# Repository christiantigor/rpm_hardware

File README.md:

rpm_hardware
============

Hardware of RPM

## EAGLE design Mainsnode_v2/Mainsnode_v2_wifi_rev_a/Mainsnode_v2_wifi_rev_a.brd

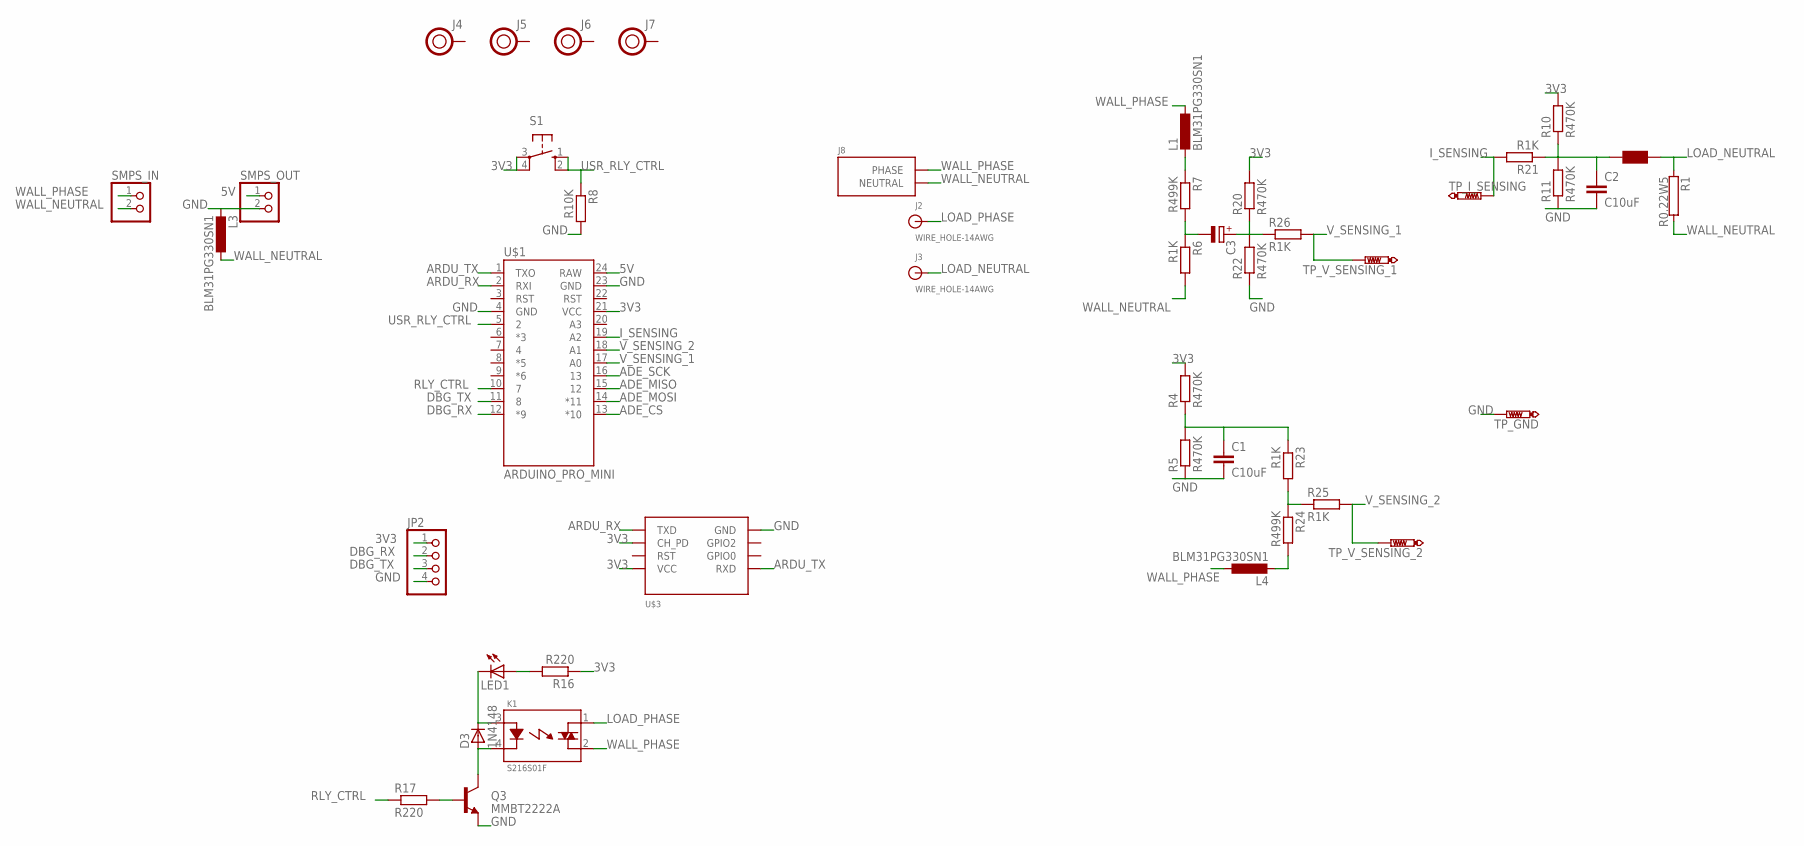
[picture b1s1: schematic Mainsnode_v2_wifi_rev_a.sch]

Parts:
C1, C2: C10uF; C0805
C3: CPOL-EU140CLH-0810; 140CLH-0810
D3: 1N4148; SOD80
J2, J3: WIRE_HOLE-14AWG
J4, J5, J6, J7: HOLE; HOLE-0.125
J8: AC-PLUG-2; AC_MALE_PINS_2
JP2: PINHD-1X4; 1X04
K1: S216S01F; RELAY_SX16S0X
L1, L3, L4: BLM31PG330SN1; L3216C
LED1: LED3MM
Q3: MMBT2222A; SOT23-3
R1: R0.22W5; KH206-8
R4, R5, R10, R11, R20, R22: R470K; R0805
R6, R21, R23, R25, R26: R1K; R0805
R7, R24: R499K; R0805
R8: R10K; R0805
R16, R17: R220; R0805
S1: 10-XX; B3F-10XX
SMPS_IN: PINHD-1X2; 1X02
SMPS_OUT: PINHD-1X2; 1X02
TP_GND: PTR1PAD1-13; P1-13
TP_I_SENSING: PTR1PAD1-13; P1-13
TP_V_SENSING_1, TP_V_SENSING_2: PTR1PAD1-13; P1-13
U$1: ARDUINO_PRO_MINI
U$2: BLM18BB151SN1; L0603
U$3: ESP8266

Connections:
3V3: JP2.1, R4.2, R10.2, R16.1, R20.2, S1.3, S1.4 (P1), U$1.21 (VCC), U$3.CH_PD, U$3.VCC
5V: SMPS_OUT.1, U$1.24 (RAW)
ADE_CS: U$1.13 (*10)
ADE_MISO: U$1.15 (12)
ADE_MOSI: U$1.14 (*11)
ADE_SCK: U$1.16 (13)
ARDU_RX: U$1.2 (RXI), U$3.TXD
ARDU_TX: U$1.1 (TXO), U$3.RXD
DBG_RX: JP2.2, U$1.12 (*9)
DBG_TX: JP2.3, U$1.11 (8)
GND: C1.2, C2.2, JP2.4, L3.2, Q3.2 (E), R5.1, R8.2, R11.1, R22.1, SMPS_OUT.2, TP_GND.TP, U$1.4 (GND), U$1.23 (GND), U$3.GND
I_SENSING: R21.2, TP_I_SENSING.TP, U$1.19 (A2)
LOAD_NEUTRAL: J3.P$1, R1.1, U$2.2
LOAD_PHASE: J2.P$1, K1.1
unnamed: C3.-, R6.1, R7.2
unnamed: C3.+, R20.1, R22.2, R26.1
unnamed: C2.1, R10.1, R11.2, R21.1, U$2.1
unnamed: C1.1, R4.1, R5.2, R23.1
unnamed: L1.2, R7.1
unnamed: R23.2, R24.1, R25.1
unnamed: LED1.A, R16.2
unnamed: L4.2, R24.2
unnamed: D3.1 (C), K1.3, LED1.K (C)
unnamed: D3.2 (A), K1.4, Q3.3 (C)
unnamed: Q3.1 (B), R17.2
RLY_CTRL: R17.1, U$1.10 (7)
USR_RLY_CTRL: R8.1, S1.1 (S), S1.2 (S1), U$1.5 (2)
V_SENSING_1: R26.2, TP_V_SENSING_1.TP, U$1.17 (A0)
V_SENSING_2: R25.2, TP_V_SENSING_2.TP, U$1.18 (A1)
WALL_NEUTRAL: J8.WALL_NEUTRAL (NEUTRAL), L3.1, R1.2, R6.2, SMPS_IN.2
WALL_PHASE: J8.WALL_PHASE (PHASE), K1.2, L1.1, L4.1, SMPS_IN.1

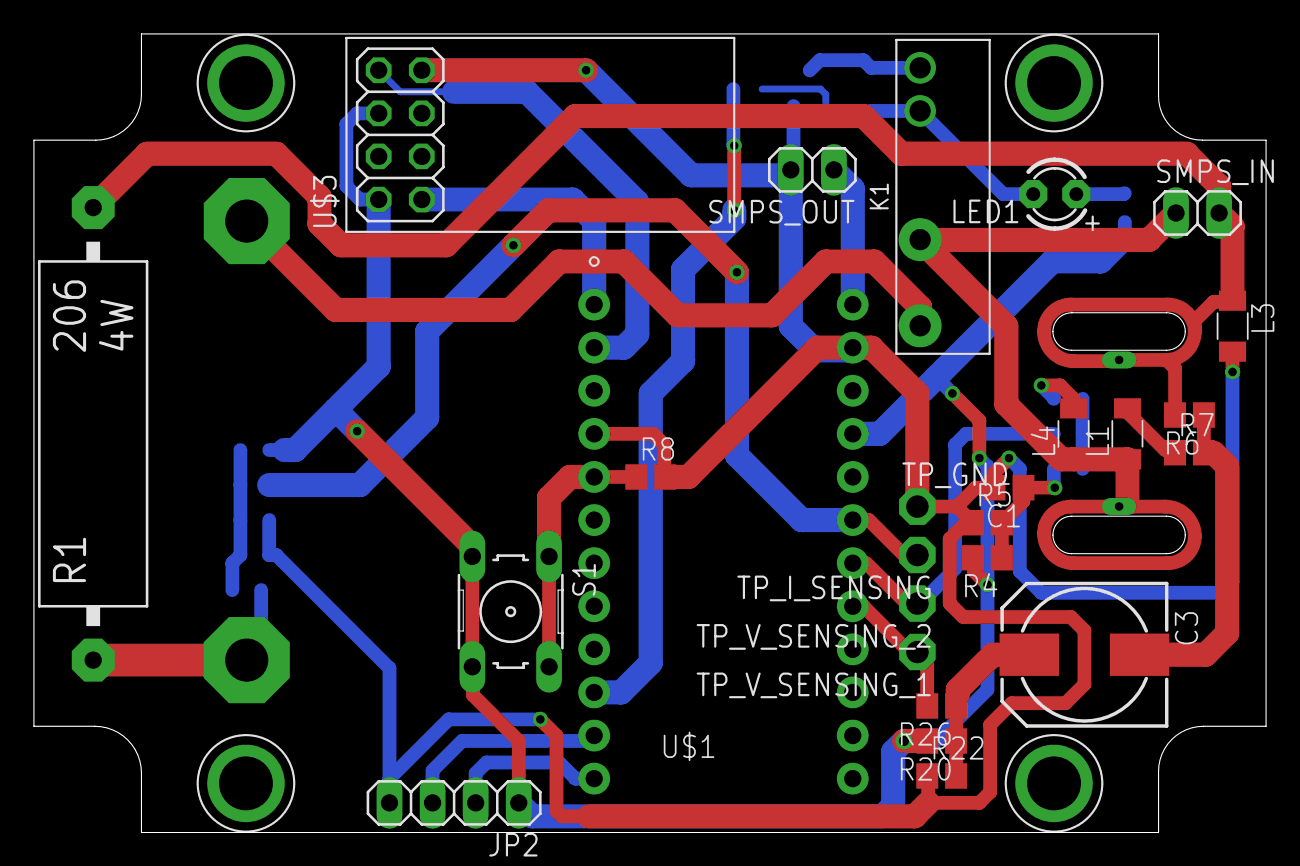
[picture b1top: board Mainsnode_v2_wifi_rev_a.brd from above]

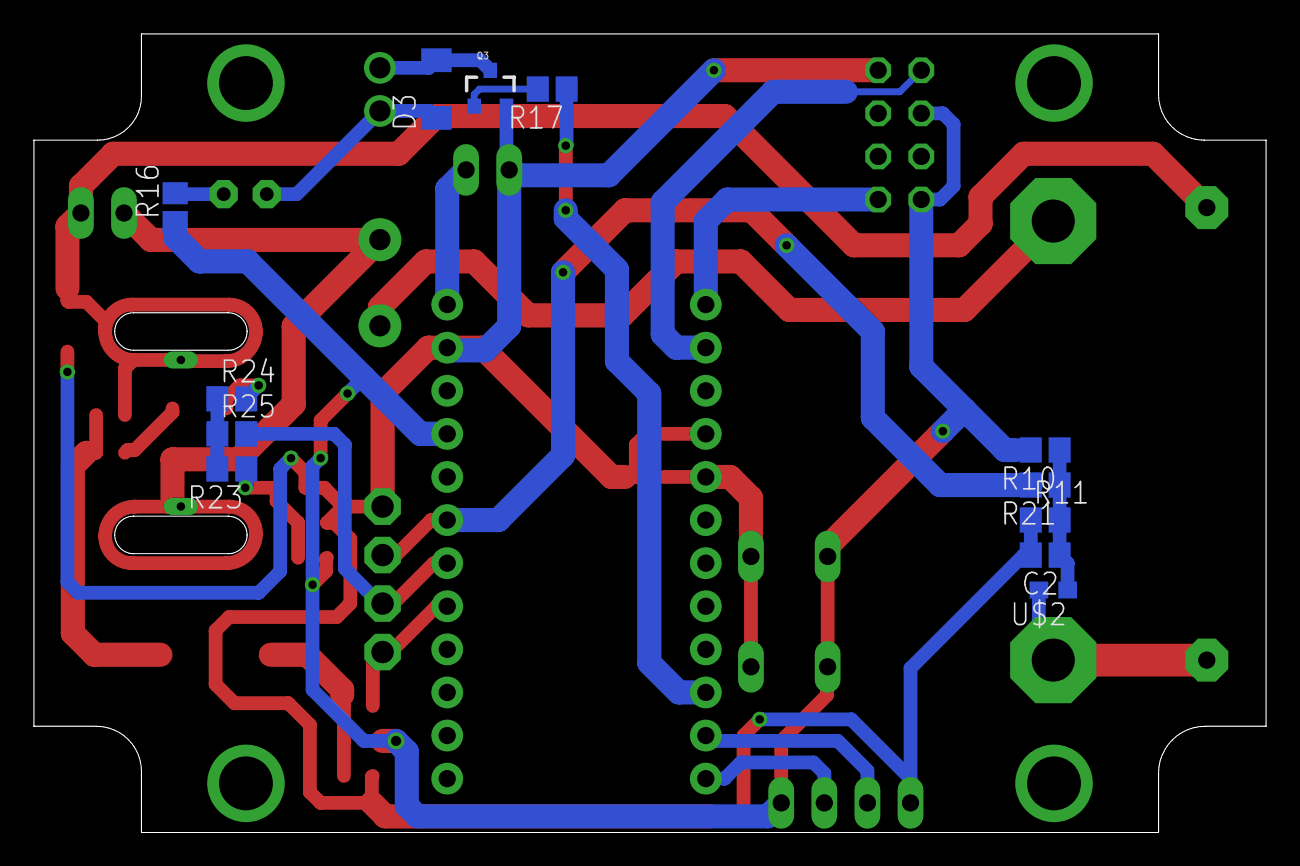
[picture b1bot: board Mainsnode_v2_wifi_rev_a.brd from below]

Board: 2 copper layers, 72.6 x 47.1 mm, 45 parts (12 on the bottom side), 27 nets.

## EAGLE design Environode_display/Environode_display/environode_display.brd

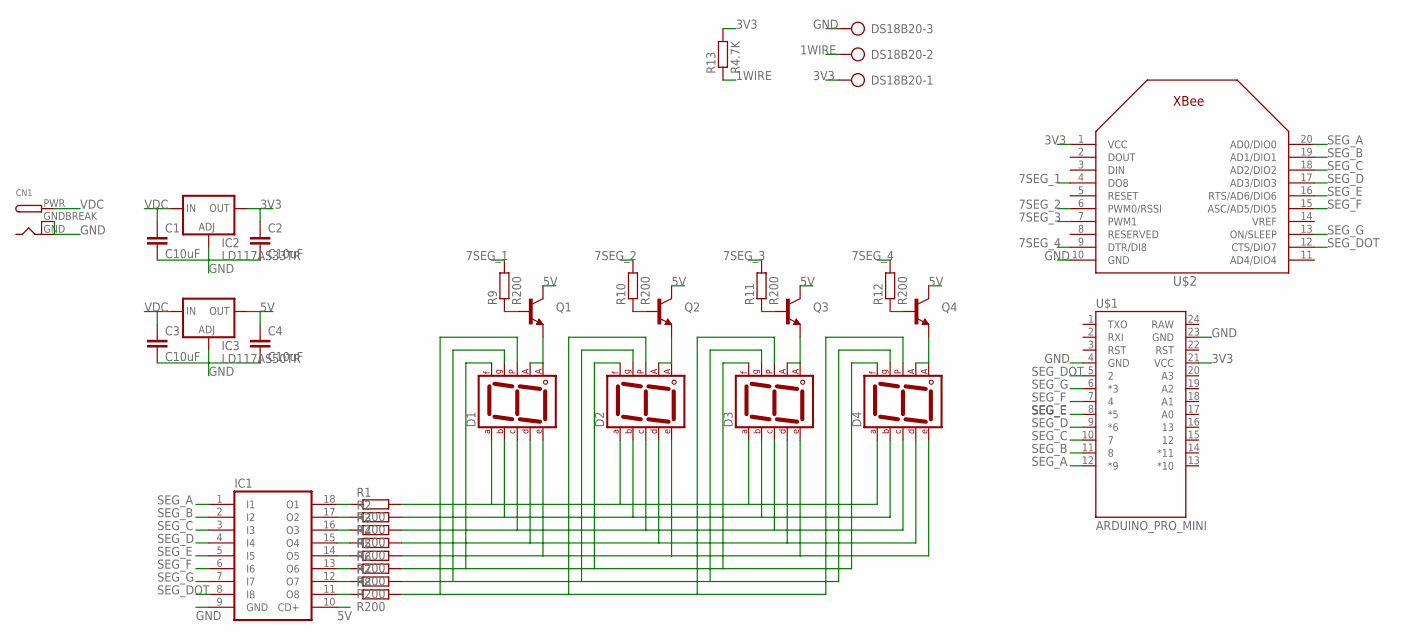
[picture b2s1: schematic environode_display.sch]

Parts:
C1, C2, C3, C4: C10uF; C0805
CN1: DCBARRELPTH; DCJACK_2MM_PTH
D1, D2, D3, D4: 7SEG-CA; 7SEG-13
DS18B20: AK300/3
IC1: ULN2803A; DIL18
IC2: LD117AS33TR; SOT223
IC3: LD117AS50TR; SOT223
Q1, Q2, Q3, Q4: TRANSISTOR_NPNP2N2222A; TO-92
R1, R2, R3, R4, R5, R6, R7, R8, R9, R10, R11, R12: R200; 0309V
R13: R4.7K; 0309V
U$1: ARDUINO_PRO_MINI
U$2: XBEE

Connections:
1WIRE: DS18B20.2, R13.1
3V3: C2.1, DS18B20.1, IC2.4 (OUT), R13.2, U$1.21 (VCC), U$2.1 (VCC)
5V: C4.1, IC1.10 (CD+), IC3.4 (OUT), Q1.1 (C), Q2.1 (C), Q3.1 (C), Q4.1 (C)
7SEG_1: R9.2, U$2.4 (DO8)
7SEG_2: R10.2, U$2.6 (PWM0/RSSI)
7SEG_3: R11.2, U$2.7 (PWM1)
7SEG_4: R12.2, U$2.9 (DTR/DI8)
GND: C1.2, C2.2, C3.2, C4.2, CN1.GND, CN1.GNDBREAK, DS18B20.3, IC1.9 (GND), IC2.1 (ADJ), IC3.1 (ADJ), U$1.4 (GND), U$1.23 (GND), U$2.10 (GND)
unnamed: IC1.18 (O1), R1.1
unnamed: IC1.17 (O2), R2.1
unnamed: IC1.16 (O3), R3.1
unnamed: IC1.15 (O4), R4.1
unnamed: IC1.14 (O5), R5.1
unnamed: IC1.13 (O6), R6.1
unnamed: IC1.12 (O7), R7.1
unnamed: IC1.11 (O8), R8.1
unnamed: D1.7 (A), D2.7 (A), D3.7 (A), D4.7 (A), R1.2
unnamed: D1.6 (B), D2.6 (B), D3.6 (B), D4.6 (B), R2.2
unnamed: D1.4 (C), D2.4 (C), D3.4 (C), D4.4 (C), R3.2
unnamed: D1.2 (D), D2.2 (D), D3.2 (D), D4.2 (D), R4.2
unnamed: D1.1 (E), D2.1 (E), D3.1 (E), D4.1 (E), R5.2
unnamed: D1.9 (F), D2.9 (F), D3.9 (F), D4.9 (F), R6.2
unnamed: D1.10 (G), D2.10 (G), D3.10 (G), D4.10 (G), R7.2
unnamed: D1.3 (CA1), D1.8 (CA2), Q1.3 (E)
unnamed: D2.3 (CA1), D2.8 (CA2), Q2.3 (E)
unnamed: Q1.2 (B), R9.1
unnamed: D1.5 (DP), D2.5 (DP), D3.5 (DP), D4.5 (DP), R8.2
unnamed: D3.3 (CA1), D3.8 (CA2), Q3.3 (E)
unnamed: Q2.2 (B), R10.1
unnamed: D4.3 (CA1), D4.8 (CA2), Q4.3 (E)
unnamed: Q3.2 (B), R11.1
unnamed: Q4.2 (B), R12.1
SEG_A: IC1.1 (I1), U$1.12 (*9), U$2.20 (AD0/DIO0)
SEG_B: IC1.2 (I2), U$1.11 (8), U$2.19 (AD1/DIO1)
SEG_C: IC1.3 (I3), U$1.10 (7), U$2.18 (AD2/DIO2)
SEG_D: IC1.4 (I4), U$1.9 (*6), U$2.17 (AD3/DIO3)
SEG_DOT: IC1.8 (I8), U$1.5 (2), U$2.12 (CTS/DIO7)
SEG_E: IC1.5 (I5), U$1.8 (*5), U$2.16 (RTS/AD6/DIO6)
SEG_F: IC1.6 (I6), U$1.7 (4), U$2.15 (ASC/AD5/DIO5)
SEG_G: IC1.7 (I7), U$1.6 (*3), U$2.13 (ON/SLEEP)
VDC: C1.1, C3.1, CN1.PWR, IC2.3 (IN), IC3.3 (IN)

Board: 2 copper layers, 32 parts (0 on the bottom side), 41 nets, no tracks yet.

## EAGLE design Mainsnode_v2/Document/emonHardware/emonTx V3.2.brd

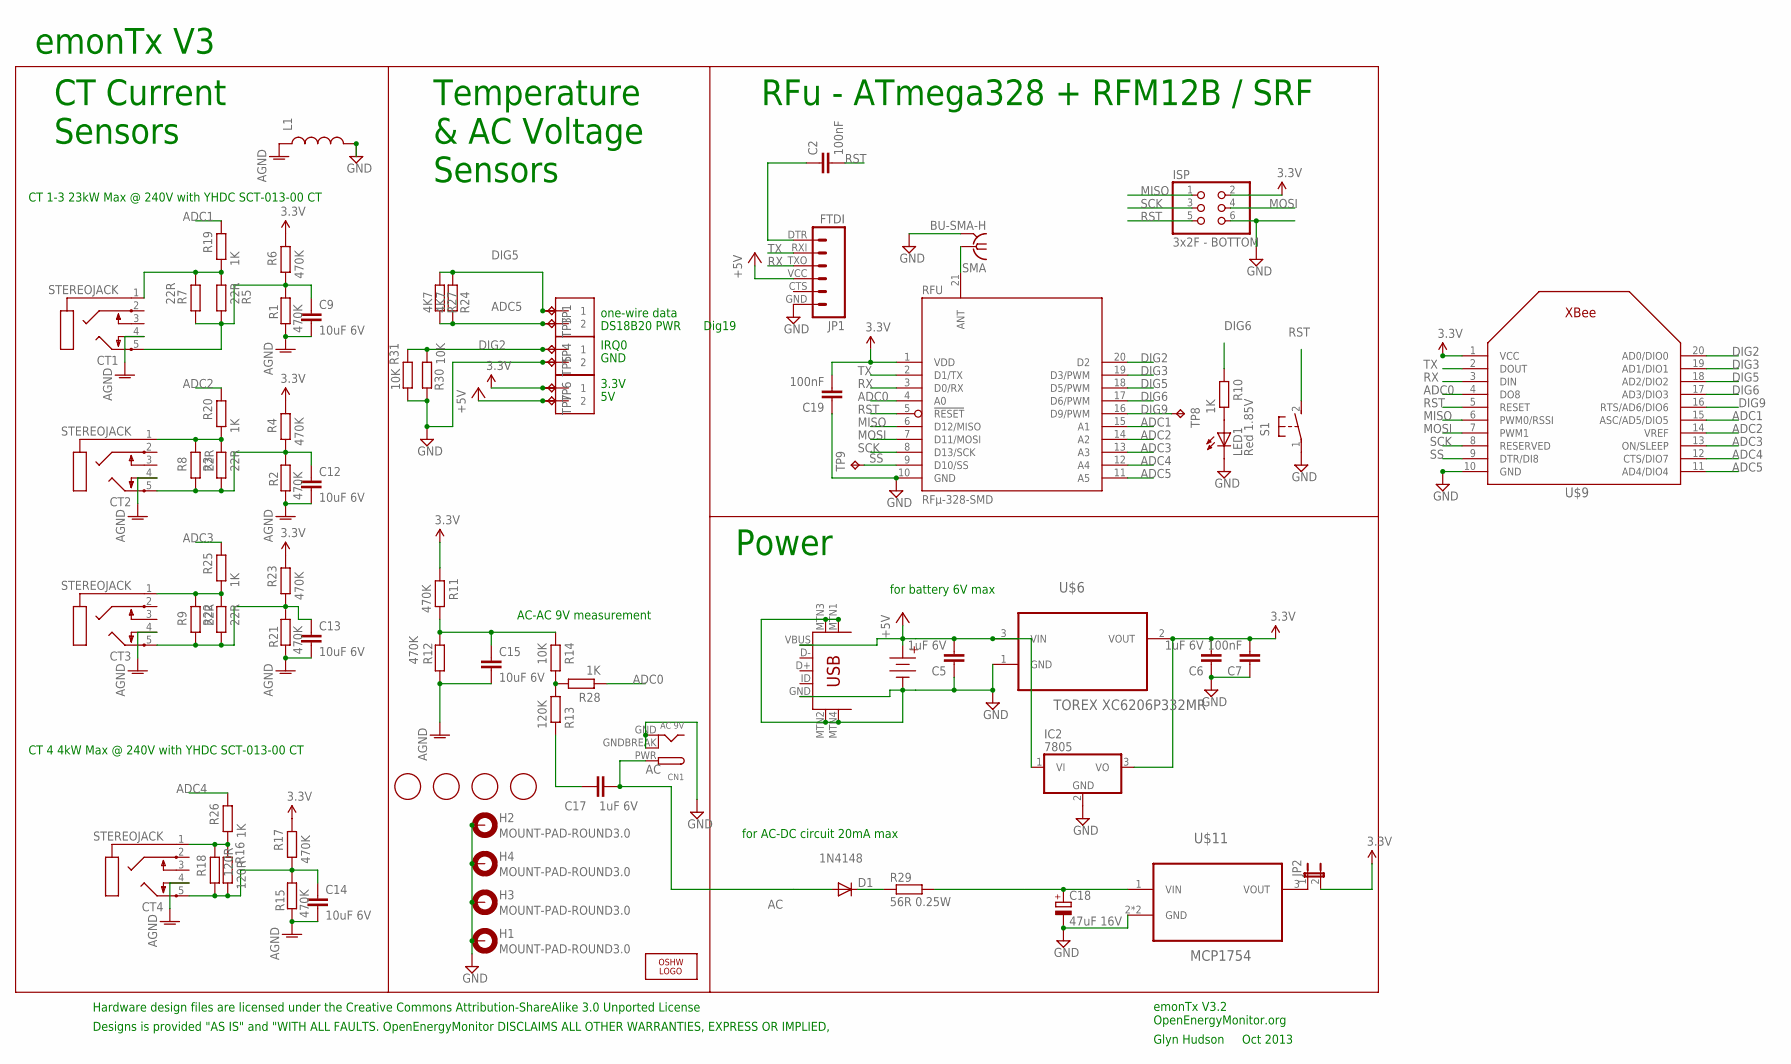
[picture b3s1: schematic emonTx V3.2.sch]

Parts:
C2, C7, C19: 100nF; C0603
C5, C6, C17: 1uF 6V; C0603
C9, C12, C13, C14, C15: 10uF 6V; C0603
C18: 47uF 16V; PANASONIC_D
CN1: AC 9V; DCJACK_2MM_PTH
CT1, CT2, CT3, CT4: STEREOJACK; STX3100
D1: 1N4148; SOD-323
H1, H2, H3, H4: MOUNT-PAD-ROUND3.0; 3,0-PAD
IC2: 7805; TO220V
ISP: 3x2F - BOTTOM; 2X03
J1, J2, J4: 1X2-3.5MM
JP1: FTDI; FTDI_BASIC
JP2: JUMPER-2PTH_LOCK; 1X02_LOCK
L1: INDUCTOR0603; 0603
LED1: Red 1.85V; CHIP-LED0805
LOGO1: OSHW_LOGO_6MILX0200-NT; OSHW_6X200_NOTEXT
R1, R2, R4, R6, R11, R12, R15, R17, R21, R23: 470K; R0603
R3, R5, R22: 22R; 0204/7
R7, R8, R9: 22R; R1206
R10, R19, R20, R25, R26, R28: 1K; R0603
R13: 120K; R0603
R14, R31: 10K; R0603
R16: 120R; 0204/7
R18: 120R; R1206
R24: 4K7; 0204/7
R27: 4K7; R0603
R29: 56R 0.25W; R1206
R30: 10K; 0204/7
RFU: RFµ-328-SMD; RFµ-328-LANDING
S1: 31-XX; B3F-31XX
SMA: BU-SMA-H
TP1, TP3, TP4, TP5, TP6, TP7, TP8, TP9: TPPAD1-13; P1-13
U$1, U$4, U$5, U$7: FIDUCIAL; FIDUCIAL_1MM
U$3: 4.5V; AAA_PCB_HOLDER
U$6: TOREX XC6206P332MR; SOT95P237X112-3N
U$9: XBEE
U$10: USB-MINIB-5PIN; USB-MINIB-CISECO
U$11: MCP1754; SOT89

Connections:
3.3V: C6.2, C7.2, C19.2, IC2.3 (VO), ISP.2, J4.1, JP2.2, R4.2, R6.2, R11.2, R17.2, R23.2, RFU.1 (VDD), TP6.TP, U$6.2 (VOUT), U$9.1 (VCC)
+5V: C5.2, IC2.1 (VI), J4.2, JP1.VCC (4), TP7.TP, U$3.+, U$6.3 (VIN), U$10.VBUS
AC: C17.2, CN1.PWR, D1.2 (A)
ADC0: R28.1, RFU.4 (A0), U$9.4 (DO8)
ADC1: R19.2, RFU.15 (A1), U$9.15 (ASC/AD5/DIO5)
ADC2: R20.2, RFU.14 (A2), U$9.14 (VREF)
ADC3: R25.2, RFU.13 (A3), U$9.13 (ON/SLEEP)
ADC4: R26.2, RFU.12 (A4), U$9.12 (CTS/DIO7)
ADC5: J2.2, R24.2, R27.2, RFU.11 (A5), TP3.TP, U$9.11 (AD4/DIO4)
AGND: C9.2, C12.2, C13.2, C14.2, C15.2, CT1.4, CT2.4, CT3.4, CT4.4, L1.1, R1.2, R2.2, R12.1, R15.2, R21.2
DIG2: J1.1, R30.1, R31.1, RFU.20 (D2), TP4.TP, U$9.20 (AD0/DIO0)
DIG3: RFU.19 (D3/PWM), U$9.19 (AD1/DIO1)
DIG5: J2.1, R24.1, R27.1, RFU.18 (D5/PWM), TP1.TP, U$9.18 (AD2/DIO2)
DIG6: R10.2, RFU.17 (D6/PWM), U$9.17 (AD3/DIO3)
DIG9: RFU.16 (D9/PWM), TP8.TP, U$9.16 (RTS/AD6/DIO6)
GND: C5.1, C6.1, C7.1, C18.-, C19.1, CN1.GND, CN1.GNDBREAK, H1.B3,0, H2.B3,0, H3.B3,0, H4.B3,0, IC2.2 (GND), ISP.6, J1.2, JP1.GND (6), L1.2, LED1.C, R30.2, R31.2, RFU.10 (GND), S1.1, SMA.2, SMA.3 (2), SMA.4 (2), SMA.5 (2), TP5.TP, U$3.-, U$6.1 (GND), U$9.10 (GND), U$10.GND, U$10.MTN1 (MTN2), U$10.MTN2 (MTN3), U$10.MTN3 (MTN1), U$10.MTN4, U$11.2 (GND), U$11.2.1 (GND)
MISO: ISP.1, RFU.6 (D12/MISO), U$9.6 (PWM0/RSSI)
MOSI: ISP.4, RFU.7 (D11/MOSI), U$9.7 (PWM1)
unnamed: CT1.1, R5.2, R7.2, R19.1
unnamed: C13.1, CT3.5, R9.1, R21.1, R22.1, R23.1
unnamed: R13.2, R14.1, R28.2
unnamed: JP2.1, U$11.3 (VOUT)
unnamed: C18.+, R29.2, U$11.1 (VIN)
unnamed: C17.1, R13.1
unnamed: CT4.1, R16.2, R18.2, R26.1
unnamed: C2.1, JP1.DTR (1)
unnamed: CT2.1, R3.2, R8.2, R20.1
unnamed: RFU.21 (ANT), SMA.1
unnamed: D1.1 (C), R29.1
unnamed: CT3.1, R9.2, R22.2, R25.1
unnamed: C12.1, CT2.5, R2.1, R3.1, R4.1, R8.1
unnamed: C15.1, R11.1, R12.2, R14.2
unnamed: C14.1, CT4.5, R15.1, R16.1, R17.1, R18.1
unnamed: C9.1, CT1.5, R1.1, R5.1, R6.1, R7.1
unnamed: LED1.A, R10.1
RST: C2.2, ISP.5, RFU.5 (!RESET), S1.2 (S), U$9.5 (RESET)
RX: JP1.TXO (3), RFU.3 (D0/RX), U$9.3 (DIN)
SCK: ISP.3, RFU.8 (D13/SCK), U$9.8 (RESERVED)
SS: RFU.9 (D10/SS), TP9.TP, U$9.9 (DTR/DI8)
TX: JP1.RXI (2), RFU.2 (D1/TX), U$9.2 (DOUT)

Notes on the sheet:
AC-AC 9V measurement
emonTx V3.2 OpenEnergyMonitor.org
Glyn Hudson Oct 2013
CT 4 4kW Max @ 240V with YHDC SCT-013-00 CT
CT 1-3 23kW Max @ 240V with YHDC SCT-013-00 CT
for battery 6V max
for AC-DC circuit 20mA max
Dig19
Power
RFu - ATmega328 + RFM12B / SRF
CT Current Sensors
Temperature & AC Voltage Sensors
Designs is provided "AS IS" and "WITH ALL FAULTS. OpenEnergyMonitor DISCLAIMS ALL OTHER WARRANTIES, EXPRESS OR IMPLIED,
Hardware design files are licensed under the Creative Commons Attribution-ShareAlike 3.0 Unported License
emonTx V3
DS18B20 PWR
one-wire data
IRQ0
GND
3.3V

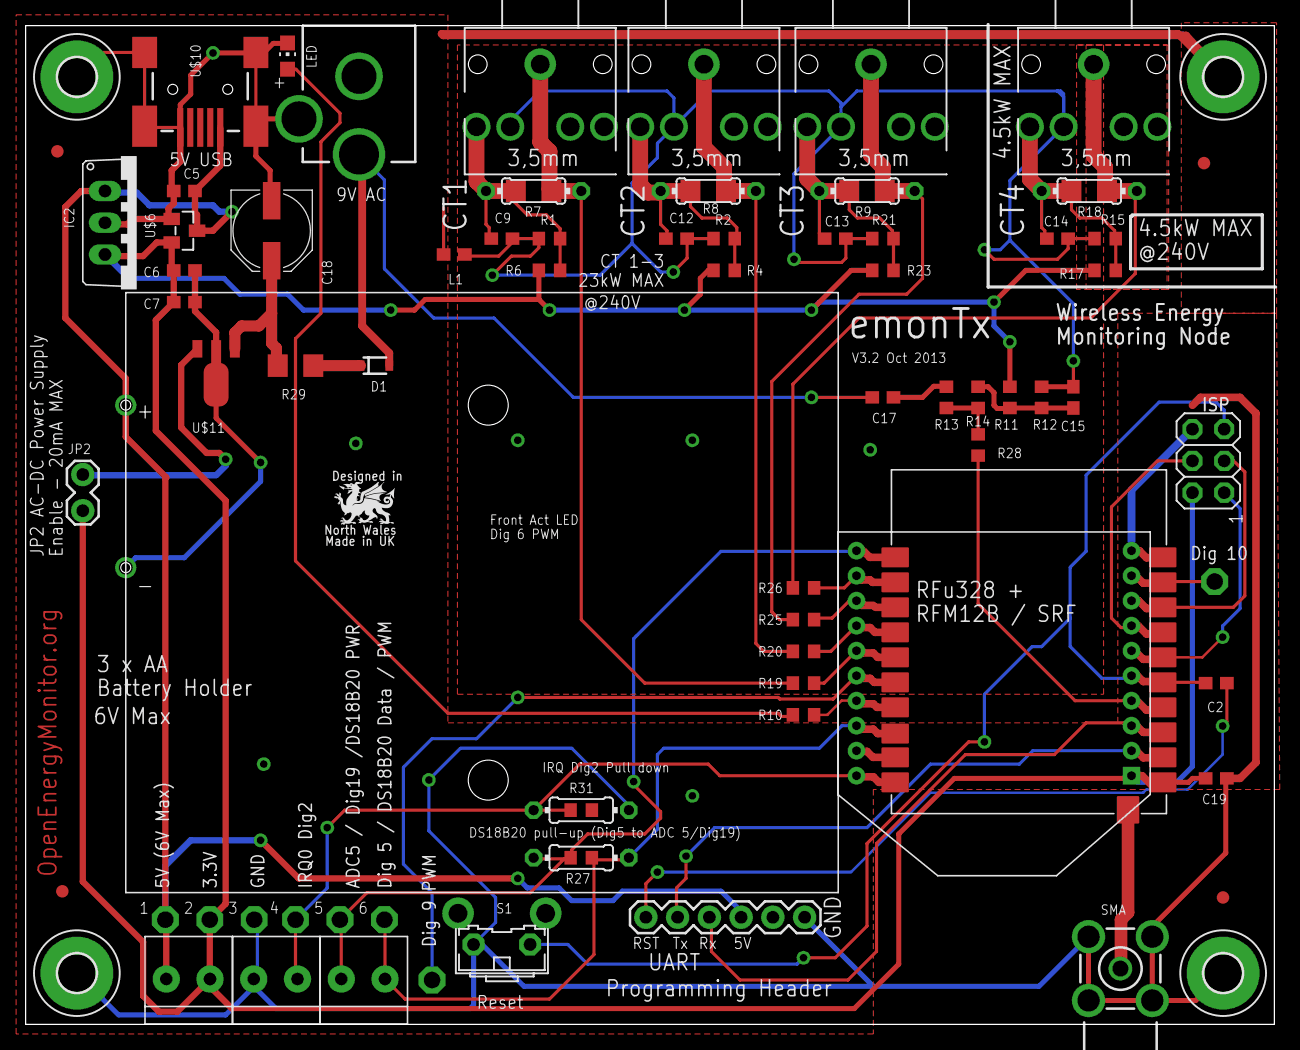
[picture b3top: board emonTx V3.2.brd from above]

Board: 2 copper layers, 99.9 x 79.9 mm, 83 parts (1 on the bottom side), 40 nets.

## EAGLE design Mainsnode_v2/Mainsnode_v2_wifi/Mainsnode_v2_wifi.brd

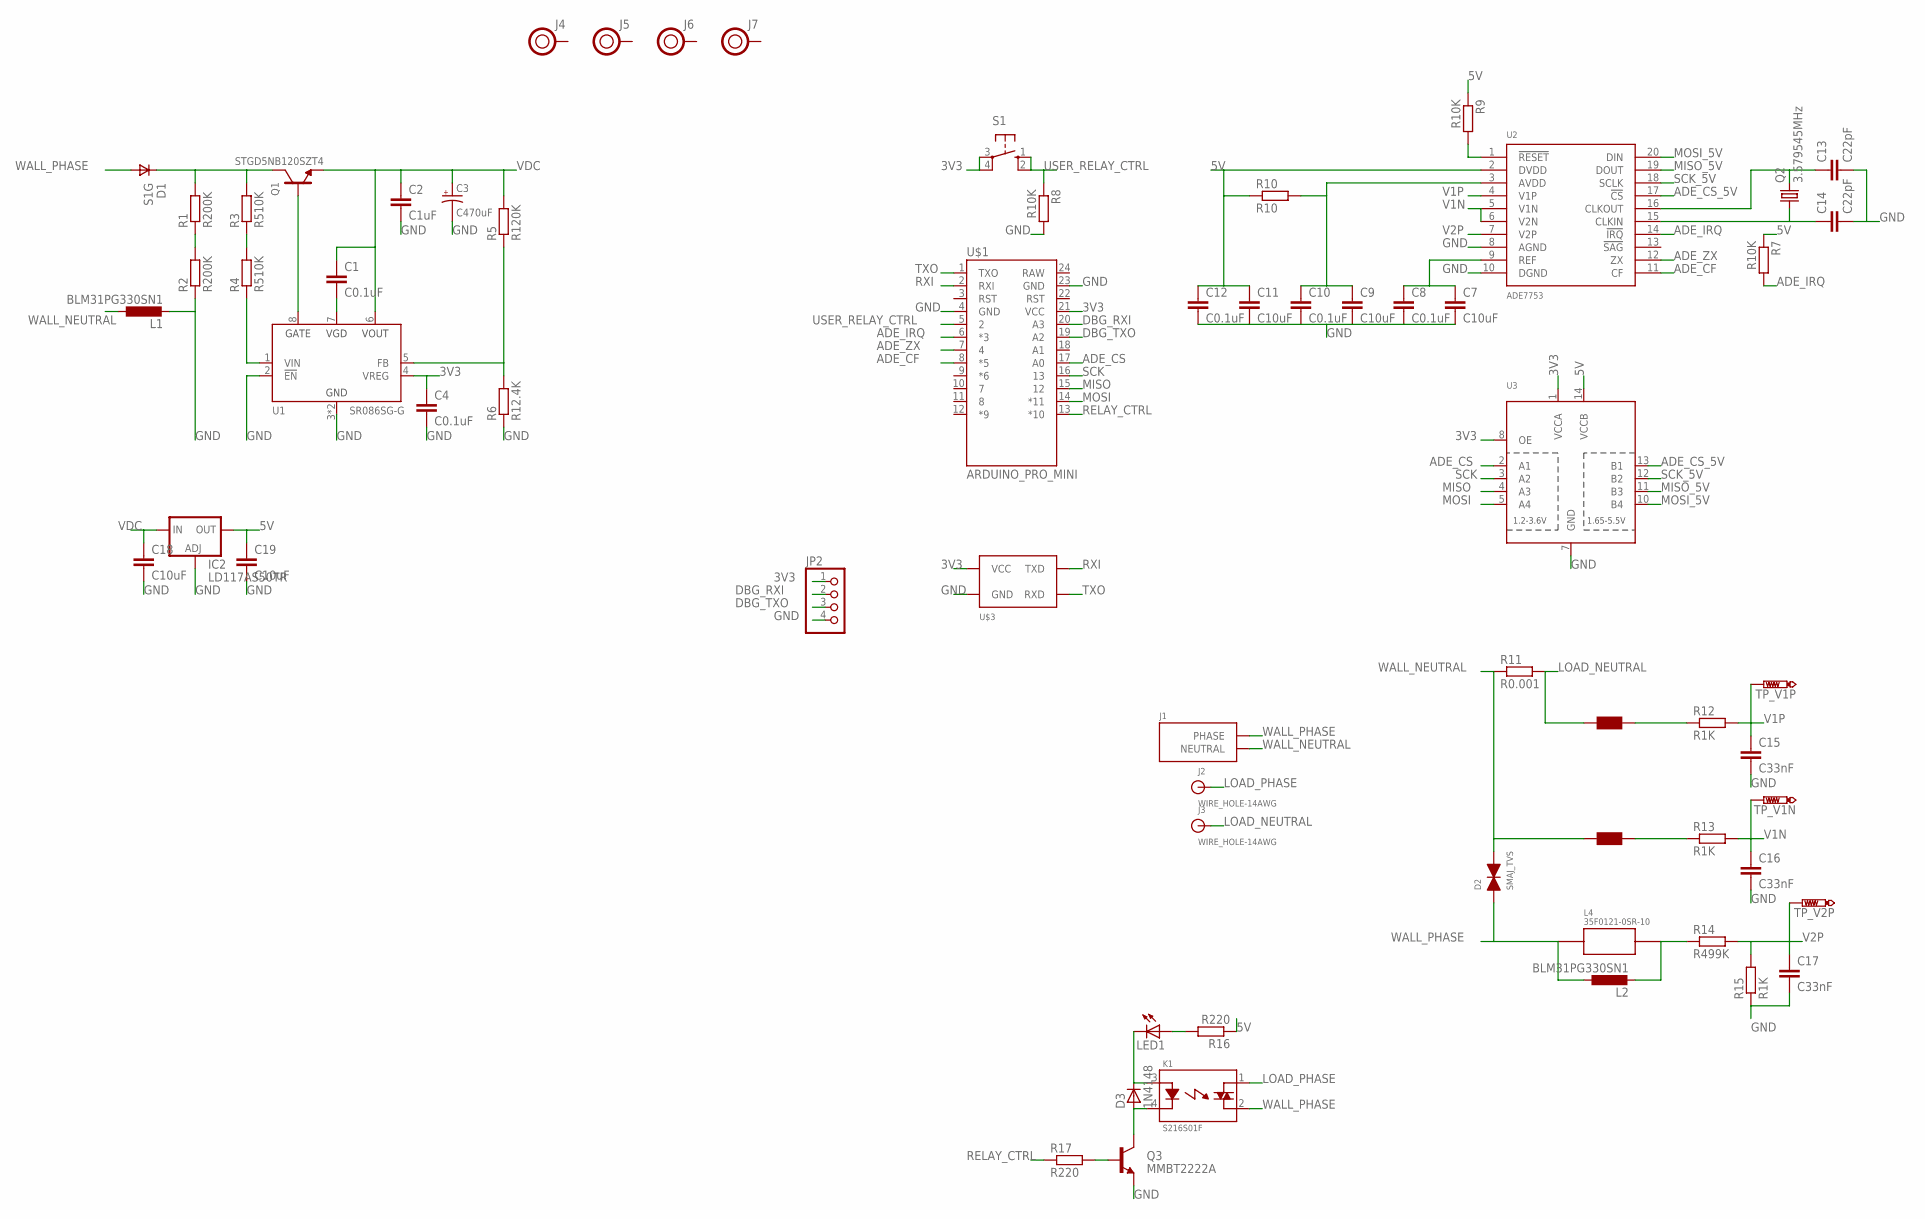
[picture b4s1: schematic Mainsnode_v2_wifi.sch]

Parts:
C1, C4, C8, C10, C12: C0.1uF; C0805
C2: C1uF; C0805
C3: C470uF; CAP_SM_10MM
C7, C9, C11, C18, C19: C10uF; C0805
C13, C14: C22pF; C0805
C15, C16, C17: C33nF; C0805
D1: S1G; DO-214AC
D2: SMAJ_TVS; DO214_TVS
D3: 1N4148; SOD80
IC2: LD117AS50TR; SOT223
J1: AC-PLUG-2; AC_MALE_PINS_2
J2, J3: WIRE_HOLE-14AWG
J4, J5, J6, J7: HOLE; HOLE-0.125
JP2: PINHD-1X4; 1X04
K1: S216S01F; RELAY_SX16S0X
L1, L2: BLM31PG330SN1; L3216C
L4: 35F0121-0SR-10; 35F0102
LED1: LED3MM
Q1: STGD5NB120SZT4; DPAK
Q2: 3.579545MHz; HC49/S
Q3: MMBT2222A; SOT23-3
R1, R2: R200K; M0805
R3, R4: R510K; M0805
R5: R120K; M0805
R6: R12.4K; M0805
R7, R8, R9: R10K; R0805
R10: R10; R0805
R11: R0.001; R2512
R12, R13, R15: R1K; R0805
R14: R499K; R0805
R16, R17: R220; R0805
S1: 10-XX; B3F-10XX
TP_V1N, TP_V1P, TP_V2P: PTR1PAD1-13; P1-13
U1: SR086SG-G; SR086
U2: ADE7753; SSOP-20
U3: TXB0104PWR; TSSOP14
U$1: ARDUINO_PRO_MINI
U$3: ESP8266
U$4, U$5: BLM18BB151SN1; L0603

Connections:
3V3: C4.1, JP2.1, S1.3, S1.4 (P1), U1.4 (VREG), U3.1 (VCCA), U3.8 (OE), U$1.21 (VCC), U$3.VCC
5V: C11.1, C12.1, C19.1, IC2.4 (OUT), R7.1, R9.1, R10.1, R16.1, U2.2 (DVDD), U3.14 (VCCB)
ADE_CF: U2.11 (CF), U$1.8 (*5)
ADE_CS: U3.2 (A1), U$1.17 (A0)
ADE_CS_5V: U2.17 (!CS), U3.13 (B1)
ADE_IRQ: R7.2, U2.14 (!IRQ), U$1.6 (*3)
ADE_ZX: U2.12 (ZX), U$1.7 (4)
DBG_RXI: JP2.2, U$1.20 (A3)
DBG_TXO: JP2.3, U$1.19 (A2)
GND: C2.2, C3.-, C4.2, C7.2, C8.2, C9.2, C10.2, C11.2, C12.2, C13.2, C14.2, C15.2, C16.2, C17.2, C18.2, C19.2, IC2.1 (ADJ), JP2.4, L1.2, Q3.2 (E), R2.1, R6.1, R8.2, R15.1, U1.2 (!EN), U1.3 (GND), U1.PAD (GND), U2.8 (AGND), U2.10 (DGND), U3.7 (GND), U$1.4 (GND), U$1.23 (GND), U$3.GND
LOAD_NEUTRAL: J3.P$1, R11.2, U$4.1
LOAD_PHASE: J2.P$1, K1.1
MISO: U3.4 (A3), U$1.15 (12)
MISO_5V: U2.19 (DOUT), U3.11 (B3)
MOSI: U3.5 (A4), U$1.14 (*11)
MOSI_5V: U2.20 (DIN), U3.10 (B4)
unnamed: D1.CATHODE, Q1.P$2 (C), R1.2, R3.2
unnamed: R1.1, R2.2
unnamed: R3.1, R4.2
unnamed: Q1.P$1 (G), U1.8 (GATE)
unnamed: R4.1, U1.1 (VIN)
unnamed: C1.2, U1.7 (VGD)
unnamed: R5.1, R6.2, U1.5 (FB)
unnamed: LED1.A, R16.2
unnamed: R9.2, U2.1 (!RESET)
unnamed: C7.1, C8.1, U2.9 (REF)
unnamed: C14.1, Q2.1, U2.15 (CLKIN)
unnamed: C13.1, Q2.2, U2.16 (CLKOUT)
unnamed: C9.1, C10.1, R10.2, U2.3 (AVDD)
unnamed: R12.1, U$4.2
unnamed: R13.1, U$5.2
unnamed: D3.1 (C), K1.3, LED1.K (C)
unnamed: L2.2, L4.2, R14.1
unnamed: D3.2 (A), K1.4, Q3.3 (C)
unnamed: Q3.1 (B), R17.2
RELAY_CTRL: R17.1, U$1.13 (*10)
RXI: U$1.2 (RXI), U$3.TXD
SCK: U3.3 (A2), U$1.16 (13)
SCK_5V: U2.18 (SCLK), U3.12 (B2)
TXO: U$1.1 (TXO), U$3.RXD
USER_RELAY_CTRL: R8.1, S1.1 (S), S1.2 (S1), U$1.5 (2)
V1N: C16.1, R13.2, TP_V1N.TP, U2.5 (V1N), U2.6 (V2N)
V1P: C15.1, R12.2, TP_V1P.TP, U2.4 (V1P)
V2P: C17.1, R14.2, R15.2, TP_V2P.TP, U2.7 (V2P)
VDC: C1.1, C2.1, C3.+, C18.1, IC2.3 (IN), Q1.P$3 (E), R5.2, U1.6 (VOUT)
WALL_NEUTRAL: D2.CATHODE, J1.NEUTRAL1 (NEUTRAL), J1.NEUTRAL2 (NEUTRAL), L1.1, R11.1, U$5.1
WALL_PHASE: D1.ANNODE, D2.ANODE, J1.PHASE1 (PHASE), J1.PHASE2 (PHASE), K1.2, L2.1, L4.1

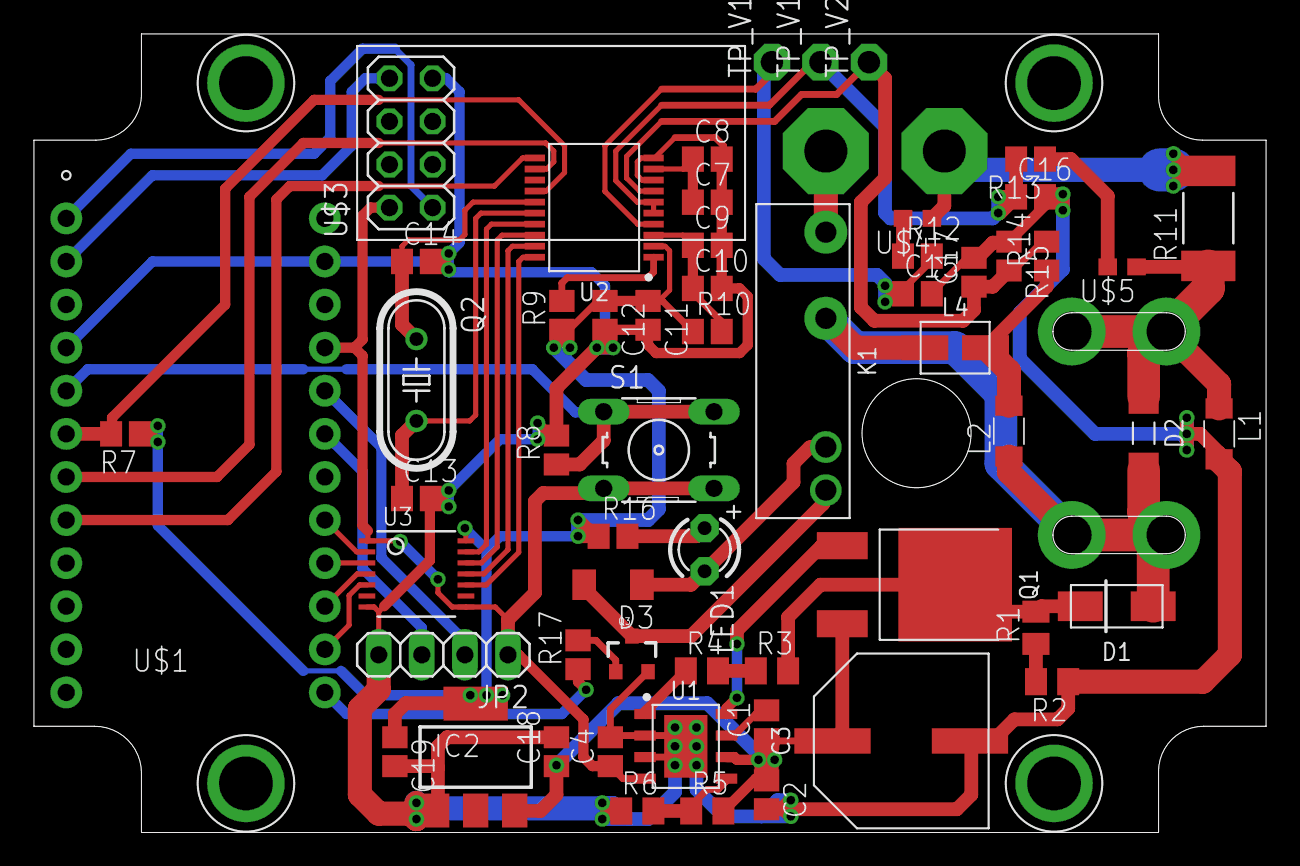
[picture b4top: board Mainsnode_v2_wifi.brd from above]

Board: 2 copper layers, 72.6 x 47.1 mm, 65 parts (0 on the bottom side), 47 nets.

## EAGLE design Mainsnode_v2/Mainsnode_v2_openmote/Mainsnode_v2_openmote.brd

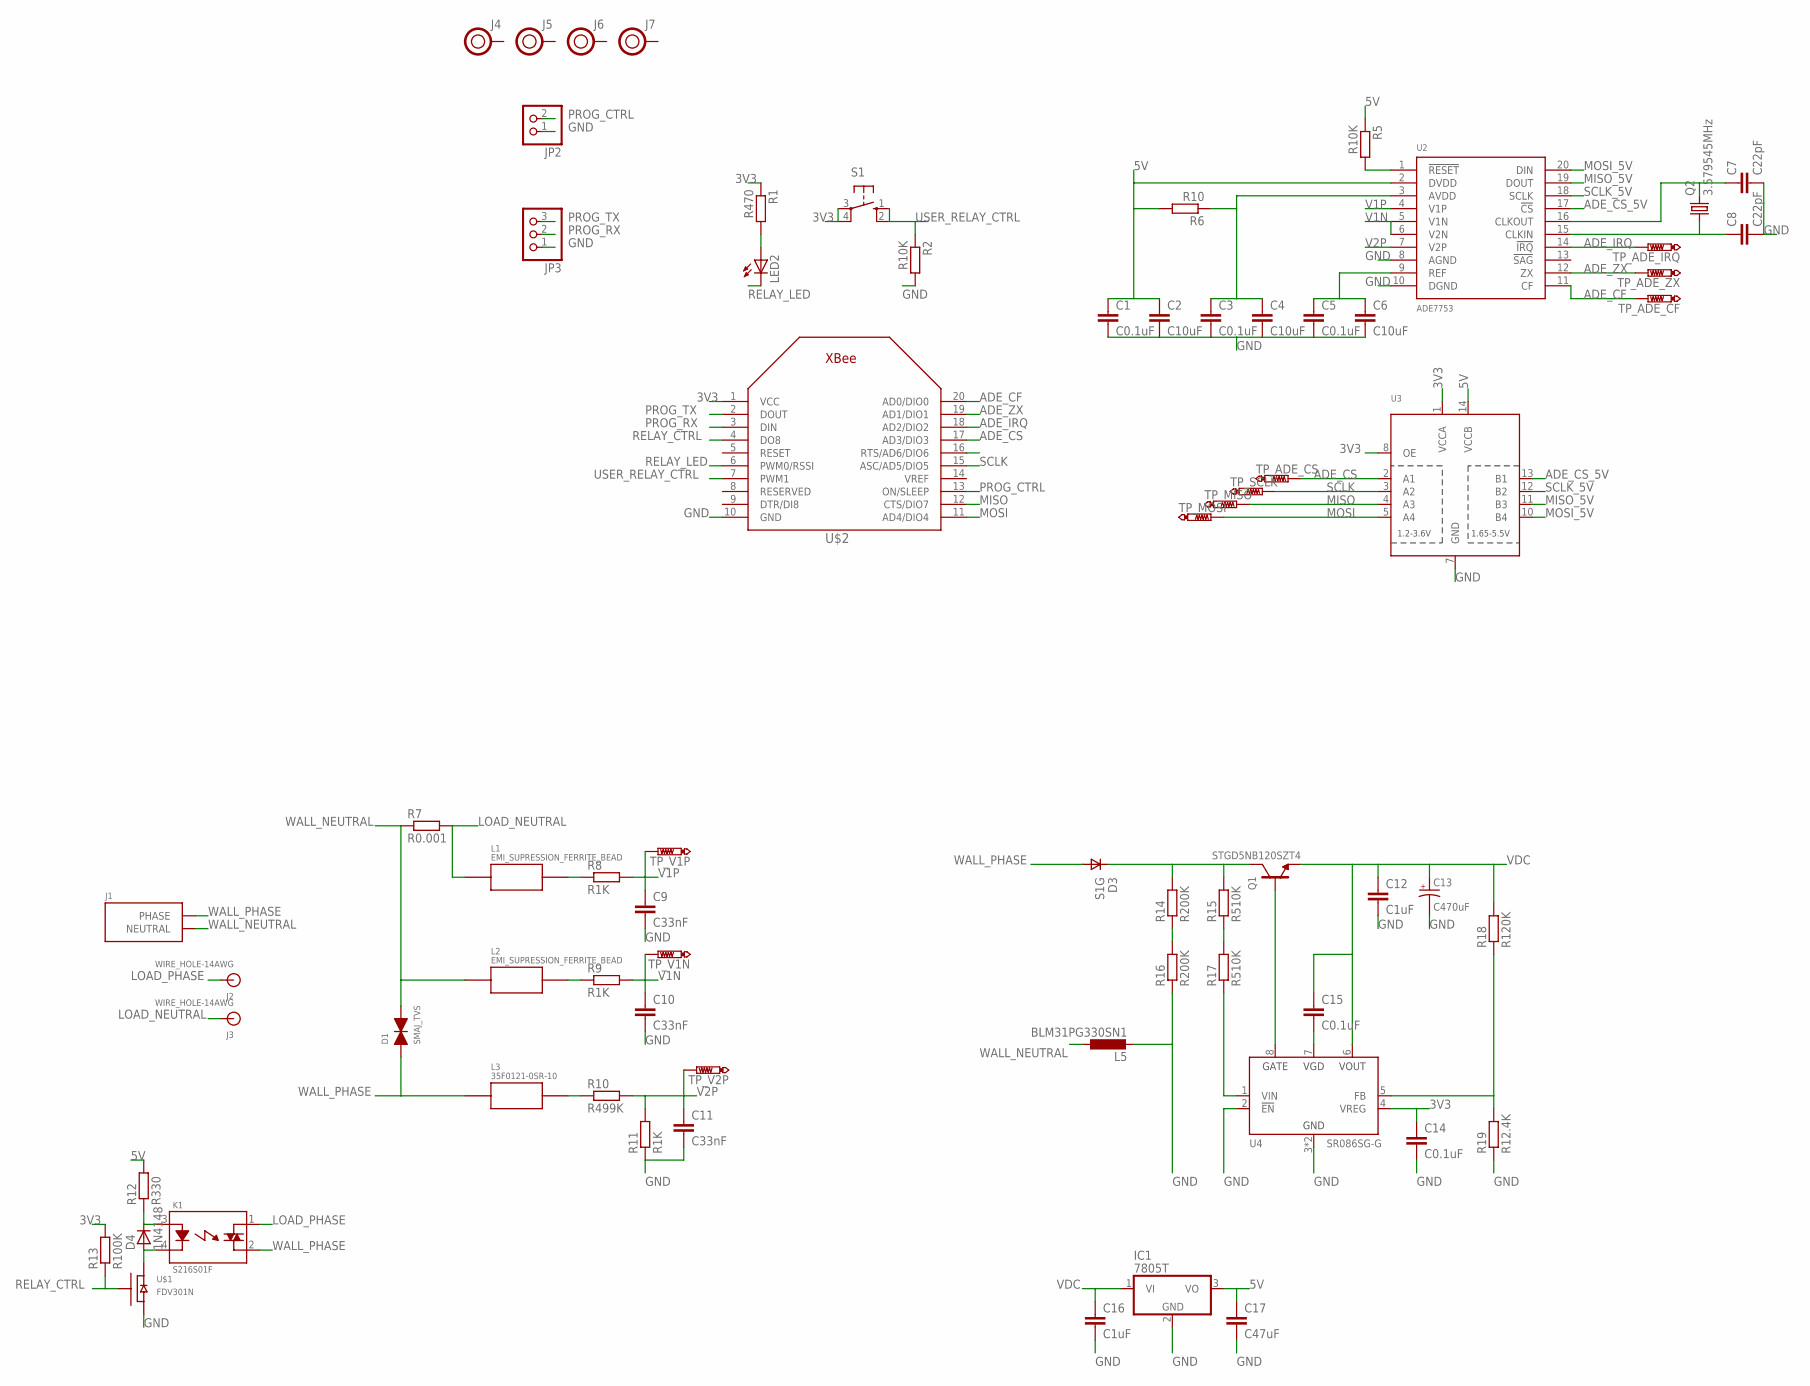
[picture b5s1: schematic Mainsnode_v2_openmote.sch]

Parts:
C1, C3, C5, C14, C15: C0.1uF; C0805
C2, C4, C6: C10uF; C0805
C7, C8: C22pF; C0805
C9, C10, C11: C33nF; C0805
C12, C16: C1uF; C0805
C13: C470uF; CAP_SM_10MM
C17: C47uF; C0805
D1: SMAJ_TVS; DO214_TVS
D3: S1G; DO-214AC
D4: 1N4148; SOD80
IC1: 7805T; TO220H
J1: AC-PLUG-2; AC_MALE_PINS_2
J2, J3: WIRE_HOLE-14AWG
J4, J5, J6, J7: HOLE; HOLE-0.125
JP2: PINHD-1X2; 1X02
JP3: PINHD-1X3; 1X03
K1: S216S01F; RELAY_SX16S0X
L1: EMI_SUPRESSION_FERRITE_BEAD; L1806
L2: EMI_SUPRESSION_FERRITE_BEAD; L1806; DIGIKEY 240-2418-1-ND
L3: 35F0121-0SR-10; 35F0102
L5: BLM31PG330SN1; L3216C
LED2: LED3MM
Q1: STGD5NB120SZT4; DPAK
Q2: 3.579545MHz; HC49/S
R1: R470; R0805
R2, R5: R10K; R0805
R6: R10; R0805
R7: R0.001; R2512
R8, R9, R11: R1K; R0805
R10: R499K; R0805
R12: R330; R0805
R13: R100K; R0805
R14, R16: R200K; R0805
R15, R17: R510K; R0805
R18: R120K; R0805
R19: R12.4K; R0805
S1: 10-XX; B3F-10XX
TP_ADE_CF: PTR1PAD1-13; P1-13
TP_ADE_CS: PTR1PAD1-13; P1-13
TP_ADE_IRQ: PTR1PAD1-13; P1-13
TP_ADE_ZX: PTR1PAD1-13; P1-13
TP_MISO: PTR1PAD1-13; P1-13
TP_MOSI: PTR1PAD1-13; P1-13
TP_SCLK: PTR1PAD1-13; P1-13
TP_V1N, TP_V1P, TP_V2P: PTR1PAD1-13; P1-13
U2: ADE7753; SSOP-20
U3: TXB0104PWR; TSSOP14
U4: SR086SG-G; SR086
U$1: FDV301N; SOT-23
U$2: XBEE

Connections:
3V3: C14.1, R1.1, R13.2, S1.3, S1.4 (P1), U3.1 (VCCA), U3.8 (OE), U4.4 (VREG), U$2.1 (VCC)
5V: C1.1, C2.1, C17.1, IC1.3 (VO), R5.1, R6.2, R12.2, U2.2 (DVDD), U3.14 (VCCB)
ADE_CF: TP_ADE_CF.TP, U2.11 (CF), U$2.20 (AD0/DIO0)
ADE_CS: TP_ADE_CS.TP, U3.2 (A1), U$2.17 (AD3/DIO3)
ADE_CS_5V: U2.17 (!CS), U3.13 (B1)
ADE_IRQ: TP_ADE_IRQ.TP, U2.14 (!IRQ), U$2.18 (AD2/DIO2)
ADE_ZX: TP_ADE_ZX.TP, U2.12 (ZX), U$2.19 (AD1/DIO1)
GND: C1.2, C2.2, C3.2, C4.2, C5.2, C6.2, C7.2, C8.2, C9.2, C10.2, C11.2, C12.2, C13.-, C14.2, C16.2, C17.2, IC1.2 (GND), JP2.1, JP3.1, L5.2, R2.2, R11.1, R16.1, R19.1, U2.8 (AGND), U2.10 (DGND), U3.7 (GND), U4.2 (!EN), U4.3 (GND), U4.PAD (GND), U$1.2 (S), U$2.10 (GND)
LOAD_NEUTRAL: J3.P$1, L1.P$1, R7.2
LOAD_PHASE: J2.P$1, K1.1
MISO: TP_MISO.TP, U3.4 (A3), U$2.12 (CTS/DIO7)
MISO_5V: U2.19 (DOUT), U3.11 (B3)
MOSI: TP_MOSI.TP, U3.5 (A4), U$2.11 (AD4/DIO4)
MOSI_5V: U2.20 (DIN), U3.10 (B4)
unnamed: D4.1 (C), K1.3, R12.1
unnamed: LED2.A, R1.2
unnamed: D4.2 (A), K1.4, U$1.3 (D)
unnamed: R5.2, U2.1 (!RESET)
unnamed: C3.1, C4.1, R6.1, U2.3 (AVDD)
unnamed: L1.P$2, R8.1
unnamed: L2.P$2, R9.1
unnamed: L3.2, R10.1
unnamed: C5.1, C6.1, U2.9 (REF)
unnamed: D3.CATHODE, Q1.P$2 (C), R14.2, R15.2
unnamed: R14.1, R16.2
unnamed: R15.1, R17.2
unnamed: R17.1, U4.1 (VIN)
unnamed: Q1.P$1 (G), U4.8 (GATE)
unnamed: C7.1, Q2.2, U2.16 (CLKOUT)
unnamed: C8.1, Q2.1, U2.15 (CLKIN)
unnamed: C15.2, U4.7 (VGD)
unnamed: R18.1, R19.2, U4.5 (FB)
PROG_CTRL: JP2.2, U$2.13 (ON/SLEEP)
PROG_RX: JP3.2, U$2.3 (DIN)
PROG_TX: JP3.3, U$2.2 (DOUT)
RELAY_CTRL: R13.1, U$1.1 (G), U$2.4 (DO8)
RELAY_LED: LED2.K (C), U$2.6 (PWM0/RSSI)
SCLK: TP_SCLK.TP, U3.3 (A2), U$2.15 (ASC/AD5/DIO5)
SCLK_5V: U2.18 (SCLK), U3.12 (B2)
USER_RELAY_CTRL: R2.1, S1.1 (S), S1.2 (S1), U$2.7 (PWM1)
V1N: C10.1, R9.2, TP_V1N.TP, U2.5 (V1N), U2.6 (V2N)
V1P: C9.1, R8.2, TP_V1P.TP, U2.4 (V1P)
V2P: C11.1, R10.2, R11.2, TP_V2P.TP, U2.7 (V2P)
VDC: C12.1, C13.+, C15.1, C16.1, IC1.1 (VI), Q1.P$3 (E), R18.2, U4.6 (VOUT)
WALL_NEUTRAL: D1.CATHODE, J1.NEUTRAL1 (NEUTRAL), J1.NEUTRAL2 (NEUTRAL), L2.P$1, L5.1, R7.1
WALL_PHASE: D1.ANODE, D3.ANNODE, J1.PHASE1 (PHASE), J1.PHASE2 (PHASE), K1.2, L3.1

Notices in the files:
parts and their libraries:
SparkFun-Electromechanical: Licensing: CC v3.0 Share-Alike You are welcome to use this library for commercial purposes.
SparkFun-DiscreteSemi: Licensing: Creative Commons ShareAlike 4.0 International - https://creativecommons.org/licenses/by-sa/4.0
